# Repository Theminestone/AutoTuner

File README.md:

# AutoTuner
TFO Meran 2023 / 2024 - Maturaprojekt

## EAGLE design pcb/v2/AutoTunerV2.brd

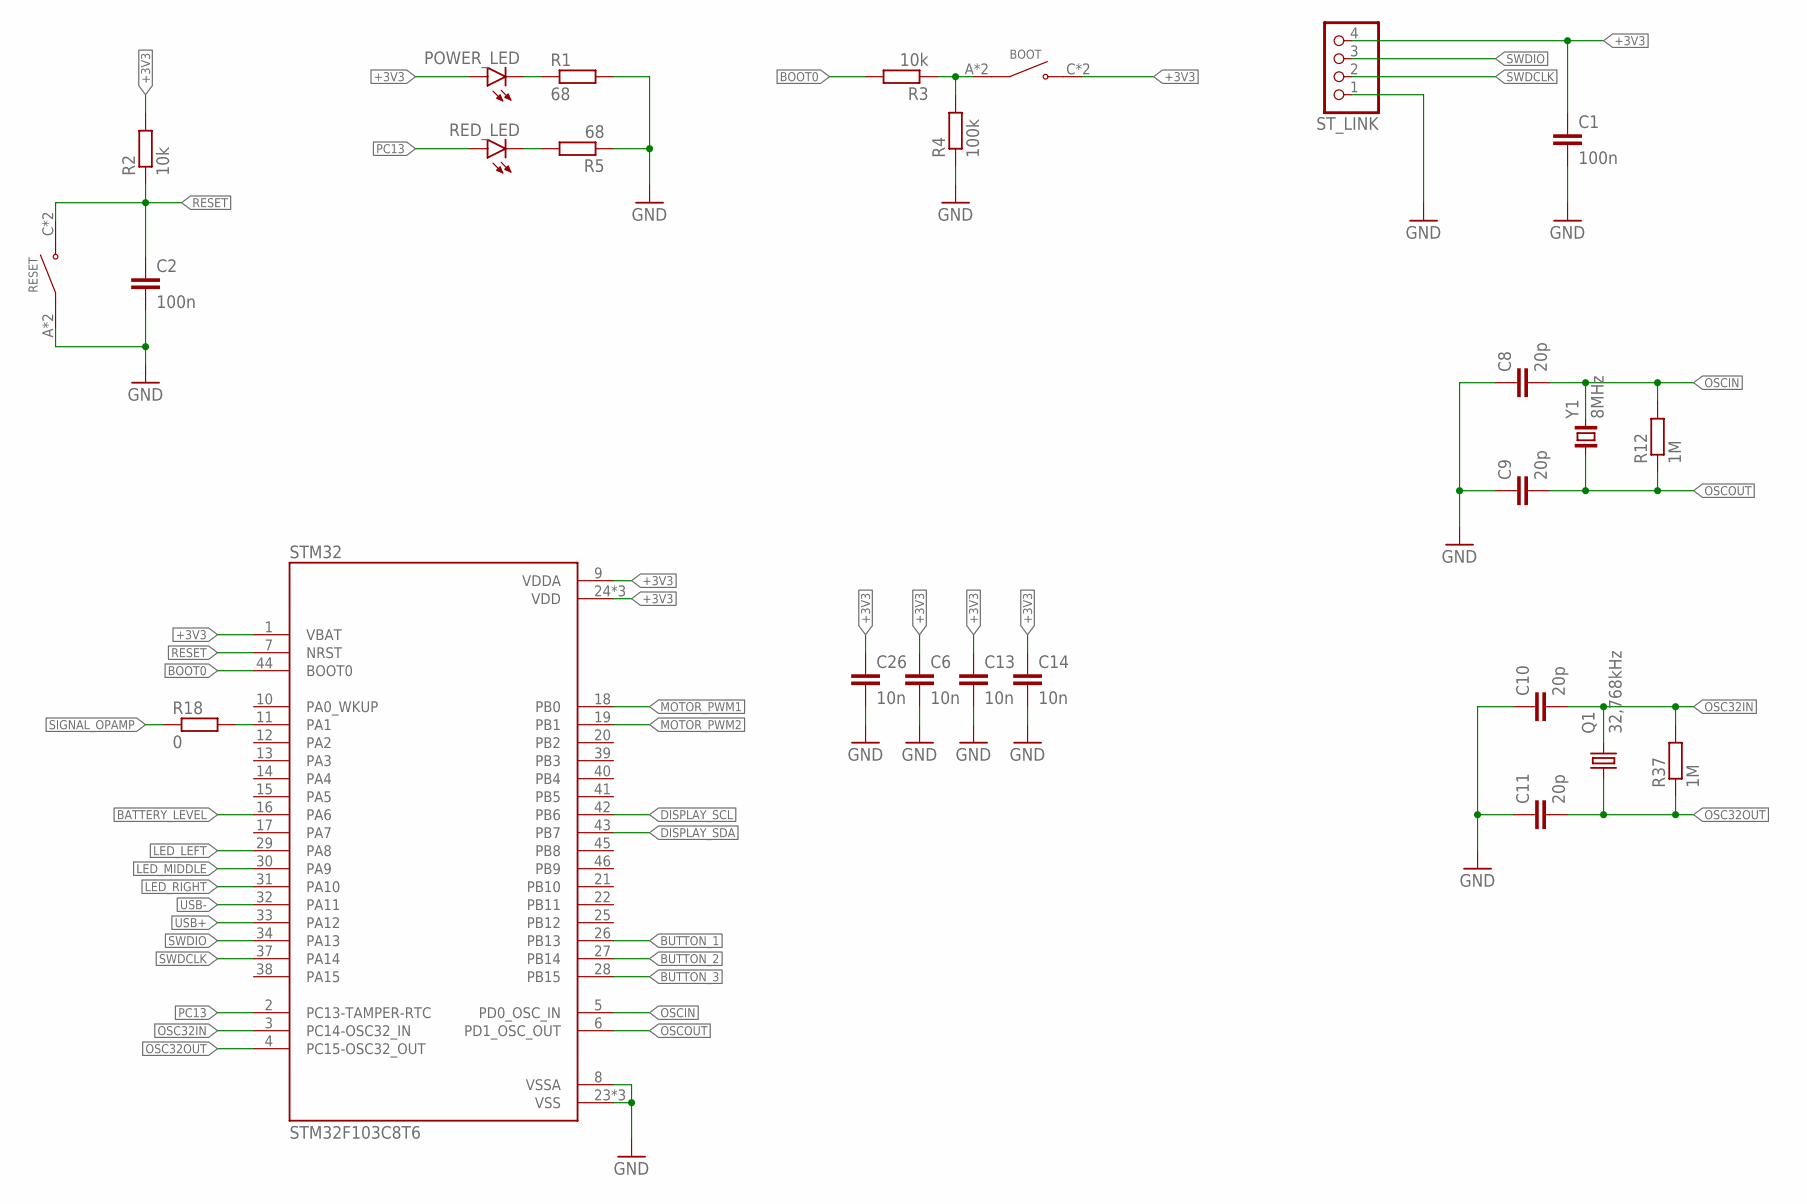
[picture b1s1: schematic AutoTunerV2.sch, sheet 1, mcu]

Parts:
BOOT: TS-1187A-B-A-B; SW_TS-1187A-B-A-B; LCSC_PART C318884
C1, C2: 100n; C0805
C6, C13, C14, C26: 10n; C0805
C8, C9, C10, C11: 20p; C0805
POWER_LED: LEDCHIPLED_0805; CHIPLED_0805; LCSC_PART C2297
Q1: 32,768kHz; 3.2X1.5; LCSC_PART C32346
R1, R5: 68; R0805; LCSC_PART C17802
R2, R3: 10k; R0805
R4: 100k; R0805
R12, R37: 1M; R0805
R18: 0; R0805
RED_LED: LEDCHIPLED_0805; CHIPLED_0805; LCSC_PART C84256
RESET: TS-1187A-B-A-B; SW_TS-1187A-B-A-B; LCSC_PART C318884
STM32: STM32F103C8T6; QFP50P900X900X160-48N; LCSC_PART C8734
ST_LINK: PINHD-1X4; 1X04
Y1: 8MHz; CRYSTAL_2-SMD-5X3; LCSC_PART C115962

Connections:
+3V3: BOOT.C (NO), BOOT.D (NO), C1.1, C6.1, C13.1, C14.1, C26.1, POWER_LED.A, R2.2, STM32.1 (VBAT), STM32.9 (VDDA), STM32.24 (VDD), STM32.36 (VDD), STM32.48 (VDD), ST_LINK.4; also elsewhere on the board
BATTERY_LEVEL: STM32.16 (PA6); also elsewhere on the board
BOOT0: R3.2, STM32.44 (BOOT0)
BUTTON_1: STM32.26 (PB13); also elsewhere on the board
BUTTON_2: STM32.27 (PB14); also elsewhere on the board
BUTTON_3: STM32.28 (PB15); also elsewhere on the board
DISPLAY_SCL: STM32.42 (PB6); also elsewhere on the board
DISPLAY_SDA: STM32.43 (PB7); also elsewhere on the board
GND: C1.2, C2.2, C6.2, C8.1, C9.1, C10.1, C11.1, C13.2, C14.2, C26.2, R1.2, R4.1, R5.1, RESET.A (COM), RESET.B (COM), STM32.8 (VSSA), STM32.23 (VSS), STM32.35 (VSS), STM32.47 (VSS), ST_LINK.1; also elsewhere on the board
LED_LEFT: STM32.29 (PA8); also elsewhere on the board
LED_MIDDLE: STM32.30 (PA9); also elsewhere on the board
LED_RIGHT: STM32.31 (PA10); also elsewhere on the board
MOTOR_PWM1: STM32.18 (PB0); also elsewhere on the board
MOTOR_PWM2: STM32.19 (PB1); also elsewhere on the board
unnamed: R5.2, RED_LED.C
unnamed: POWER_LED.C, R1.1
unnamed: BOOT.A (COM), BOOT.B (COM), R3.1, R4.2
unnamed: R18.2, STM32.11 (PA1)
OSC32IN: C10.2, Q1.2, R37.2, STM32.3 (PC14-OSC32_IN)
OSC32OUT: C11.2, Q1.1, R37.1, STM32.4 (PC15-OSC32_OUT)
OSCIN: C8.2, R12.2, STM32.5 (PD0_OSC_IN), Y1.2
OSCOUT: C9.2, R12.1, STM32.6 (PD1_OSC_OUT), Y1.1
PC13: RED_LED.A, STM32.2 (PC13-TAMPER-RTC)
RESET: C2.1, R2.1, RESET.C (NO), RESET.D (NO), STM32.7 (NRST)
SIGNAL_OPAMP: R18.1; also elsewhere on the board
SWDCLK: STM32.37 (PA14), ST_LINK.2
SWDIO: STM32.34 (PA13), ST_LINK.3
USB+: STM32.33 (PA12); also elsewhere on the board
USB-: STM32.32 (PA11); also elsewhere on the board

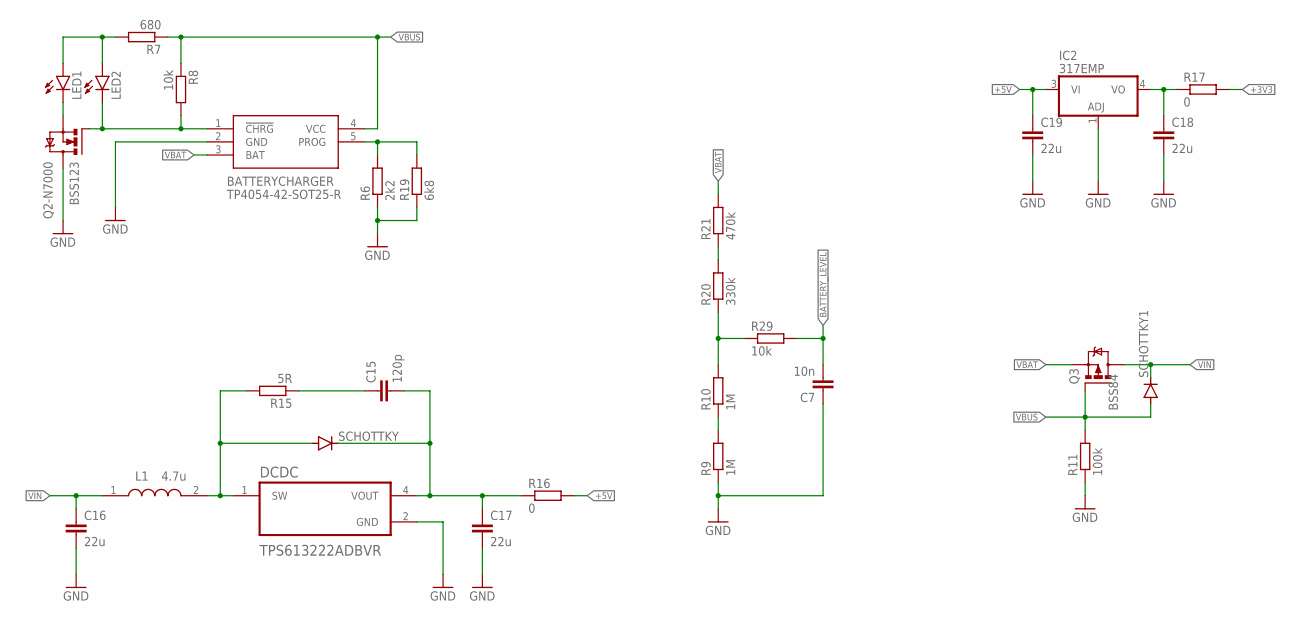
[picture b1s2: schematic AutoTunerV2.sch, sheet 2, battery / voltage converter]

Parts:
BATTERYCHARGER: TP4054-42-SOT25-R; SOT95P280X100-5N; LCSC_PART C32574
C7: 10n; C0805
C15: 120p; C0805
C16, C17, C18, C19: 22u; C1206; LCSC_PART C5672
DCDC: TPS613222ADBVR; SOT95P280X145-5N; LCSC_PART C2071163
IC2: 317EMP; SOT223; LCSC_PART C6186
L1: 4.7u; DFE2HCAH1R0MJ0L; LCSC_PART C3093670
LED1: LEDCHIPLED_0805; CHIPLED_0805; LCSC_PART C2297
LED2: LEDCHIPLED_0805; CHIPLED_0805; LCSC_PART C84256
Q2-N7000: BSS123; SOT23; LCSC_PART C20917
Q3: BSS84; SOT23; LCSC_PARTS C10487
R6: 2k2; R0805
R7: 680; R0805
R8, R29: 10k; R0805
R9, R10: 1M; R0805
R11: 100k; R0805
R15: 5R; R0805
R16, R17: 0; R0805
R19: 6k8; R0805
R20: 330k; R0805
R21: 470k; R0805
SCHOTTKY, SCHOTTKY1: DIODE-SOD323-R; SOD323-R; LCSC_PART C191023

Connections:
+3V3: R17.2; also elsewhere on the board
+5V: C19.1, IC2.3 (VI), R16.2; also elsewhere on the board
BATTERY_LEVEL: C7.2, R29.2; also elsewhere on the board
GND: BATTERYCHARGER.2 (GND), C7.1, C16.2, C17.2, C18.2, C19.2, DCDC.2 (GND), IC2.1 (ADJ), Q2-N7000.3 (D), R6.1, R9.1, R11.1, R19.1; also elsewhere on the board
unnamed: DCDC.1 (SW), L1.2, R15.2, SCHOTTKY.A
unnamed: R9.2, R10.1
unnamed: C15.2, C17.1, DCDC.4 (VOUT), R16.1, SCHOTTKY.C
unnamed: BATTERYCHARGER.5 (PROG), R6.2, R19.2
unnamed: BATTERYCHARGER.1 (!CHRG), LED2.C, Q2-N7000.1 (G), R8.2
unnamed: C15.1, R15.1
unnamed: LED1.A, LED2.A, R7.2
unnamed: LED1.C, Q2-N7000.2 (S)
unnamed: C18.1, IC2.4 (VO), R17.1
unnamed: R20.2, R21.1
unnamed: R10.2, R20.1, R29.1
VBAT: BATTERYCHARGER.3 (BAT), Q3.2 (S), R21.2; also elsewhere on the board
VBUS: BATTERYCHARGER.4 (VCC), Q3.1 (G), R7.1, R8.1, R11.2, SCHOTTKY1.A; also elsewhere on the board
VIN: C16.1, L1.1, Q3.3 (D), SCHOTTKY1.C

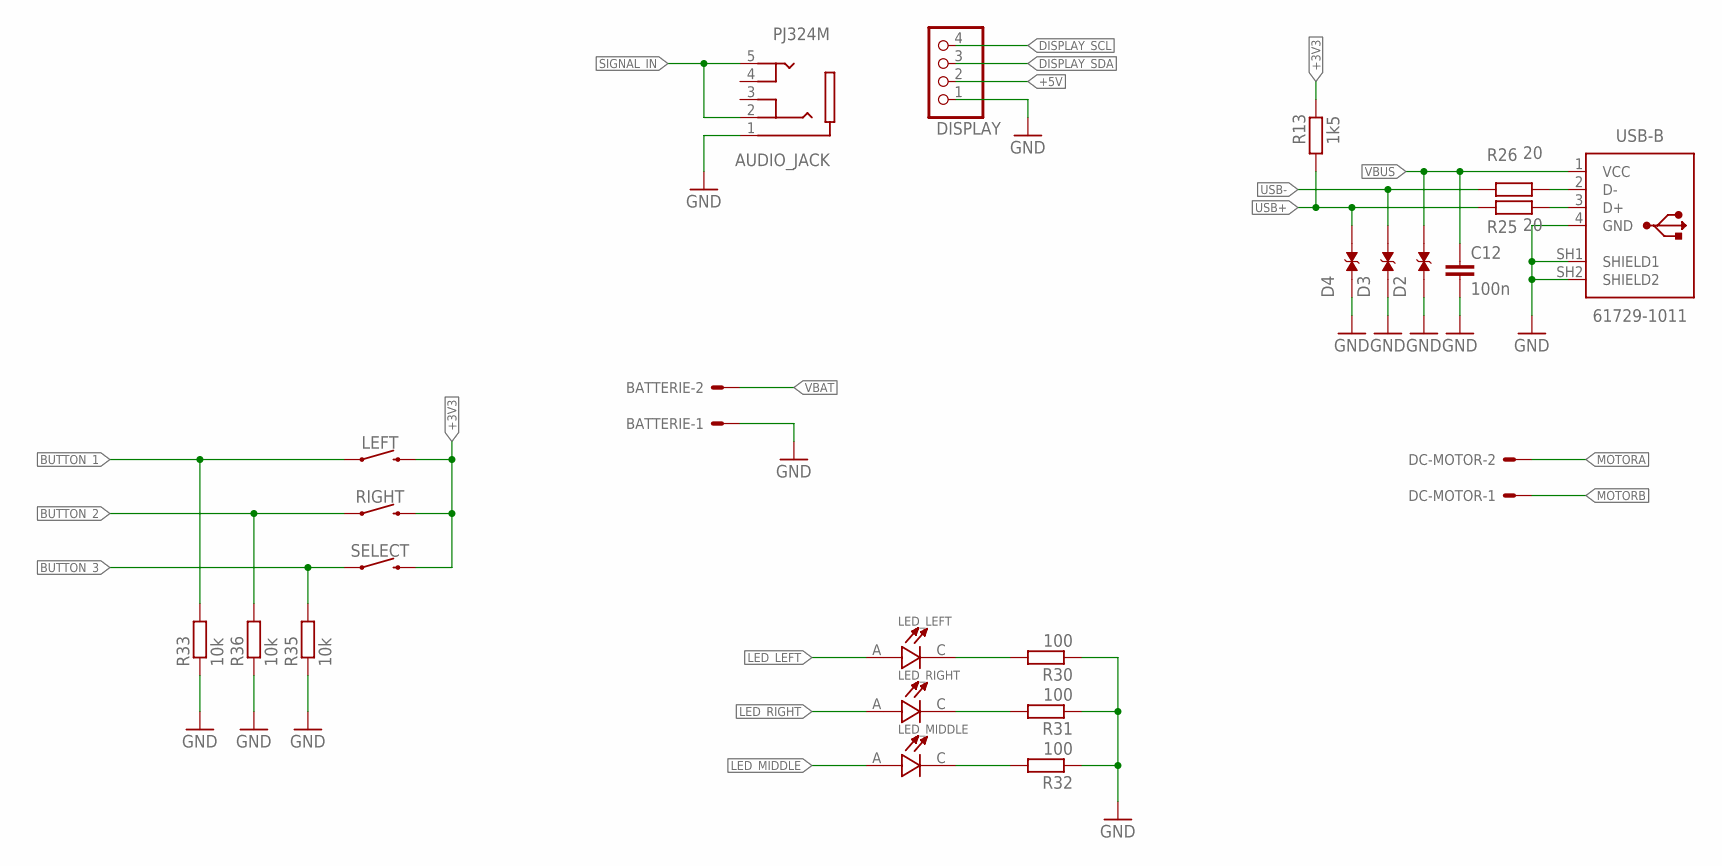
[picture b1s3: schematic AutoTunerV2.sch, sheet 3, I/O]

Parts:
AUDIO_JACK: PJ324M; WENZHOU_PJ324M
BATTERIE: 22-27-2021-02; 6410-02
C12: 100n; C0805
D2, D3, D4: TESD5V0L1UC_RJG; DIO_TESD5V0L1UC_RJG; LCSC_PART C7420372
DC-MOTOR: 22-27-2021-02; 6410-02
DISPLAY: PINHD-1X4; 1X04
LED_LEFT: L-53GD; LEDRD254W50D500H1060
LED_MIDDLE: L-53GD; LEDRD254W50D500H1060
LED_RIGHT: L-53GD; LEDRD254W50D500H1060
LEFT: MOMENTARY-SWITCH-SPST-PTH-12MM; TACTILE_SWITCH_PTH_12MM
R13: 1k5; R0805
R25, R26: 20; R0805
R30, R31, R32: 100; R0805
R33, R35, R36: 10k; R0805
RIGHT: MOMENTARY-SWITCH-SPST-PTH-12MM; TACTILE_SWITCH_PTH_12MM
SELECT: MOMENTARY-SWITCH-SPST-PTH-12MM; TACTILE_SWITCH_PTH_12MM
USB-B: 61729-1011; 61729-1011BLF

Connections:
+3V3: LEFT.3 (2), R13.2, RIGHT.3 (2), SELECT.3 (2); also elsewhere on the board
+5V: DISPLAY.2; also elsewhere on the board
BUTTON_1: LEFT.1, R33.2; also elsewhere on the board
BUTTON_2: R36.2, RIGHT.1; also elsewhere on the board
BUTTON_3: R35.2, SELECT.1; also elsewhere on the board
DISPLAY_SCL: DISPLAY.4; also elsewhere on the board
DISPLAY_SDA: DISPLAY.3; also elsewhere on the board
GND: AUDIO_JACK.1 (SLEEVE), BATTERIE.1, C12.2, D2.1, D3.1, D4.1, DISPLAY.1, R30.1, R31.1, R32.1, R33.1, R35.1, R36.1, USB-B.4 (GND), USB-B.SH1 (SHIELD1), USB-B.SH2 (SHIELD2); also elsewhere on the board
LED_LEFT: LED_LEFT.A; also elsewhere on the board
LED_MIDDLE: LED_MIDDLE.A; also elsewhere on the board
LED_RIGHT: LED_RIGHT.A; also elsewhere on the board
MOTORA: DC-MOTOR.2; also elsewhere on the board
MOTORB: DC-MOTOR.1; also elsewhere on the board
unnamed: LED_LEFT.C, R30.2
unnamed: LED_RIGHT.C, R31.2
unnamed: LED_MIDDLE.C, R32.2
unnamed: R25.2, USB-B.3 (D+)
unnamed: R26.2, USB-B.2 (D-)
SIGNAL_IN: AUDIO_JACK.2 (RING_1), AUDIO_JACK.5 (TIP_2); also elsewhere on the board
USB+: D4.2, R13.1, R25.1; also elsewhere on the board
USB-: D3.2, R26.1; also elsewhere on the board
VBAT: BATTERIE.2; also elsewhere on the board
VBUS: C12.1, D2.2, USB-B.1 (VCC); also elsewhere on the board

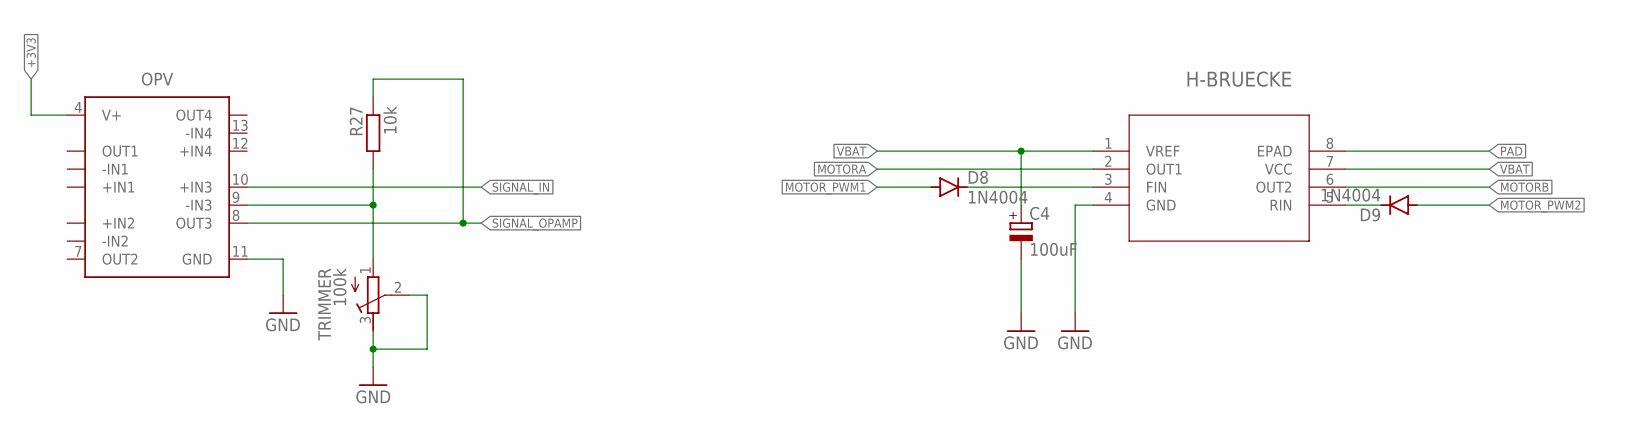
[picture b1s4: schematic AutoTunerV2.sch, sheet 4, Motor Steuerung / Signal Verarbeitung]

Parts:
C4: 100uF; B45181A
D8, D9: 1N4004; DO41-10
H-BRUECKE: BD6222HFP-TRHRP7_ROM-M; HRP7_ROM-M
OPV: LM324_SOIC; SOIC127P600X175-14N; LCSC_PART C71035
R27: 10k; R0805
TRIMMER: 100k; RTRIM64Y

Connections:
+3V3: OPV.4 (V+); also elsewhere on the board
GND: C4.-, H-BRUECKE.4 (GND), OPV.11 (GND), TRIMMER.2 (S), TRIMMER.3 (E); also elsewhere on the board
MOTORA: H-BRUECKE.2 (OUT1); also elsewhere on the board
MOTORB: H-BRUECKE.6 (OUT2); also elsewhere on the board
MOTOR_PWM1: D8.A; also elsewhere on the board
MOTOR_PWM2: D9.A; also elsewhere on the board
unnamed: D8.C, H-BRUECKE.3 (FIN)
unnamed: D9.C, H-BRUECKE.5 (RIN)
unnamed: OPV.9 (-IN3), R27.2, TRIMMER.1 (A)
PAD: H-BRUECKE.8 (EPAD)
SIGNAL_IN: OPV.10 (+IN3); also elsewhere on the board
SIGNAL_OPAMP: OPV.8 (OUT3), R27.1; also elsewhere on the board
VBAT: C4.+, H-BRUECKE.1 (VREF), H-BRUECKE.7 (VCC); also elsewhere on the board

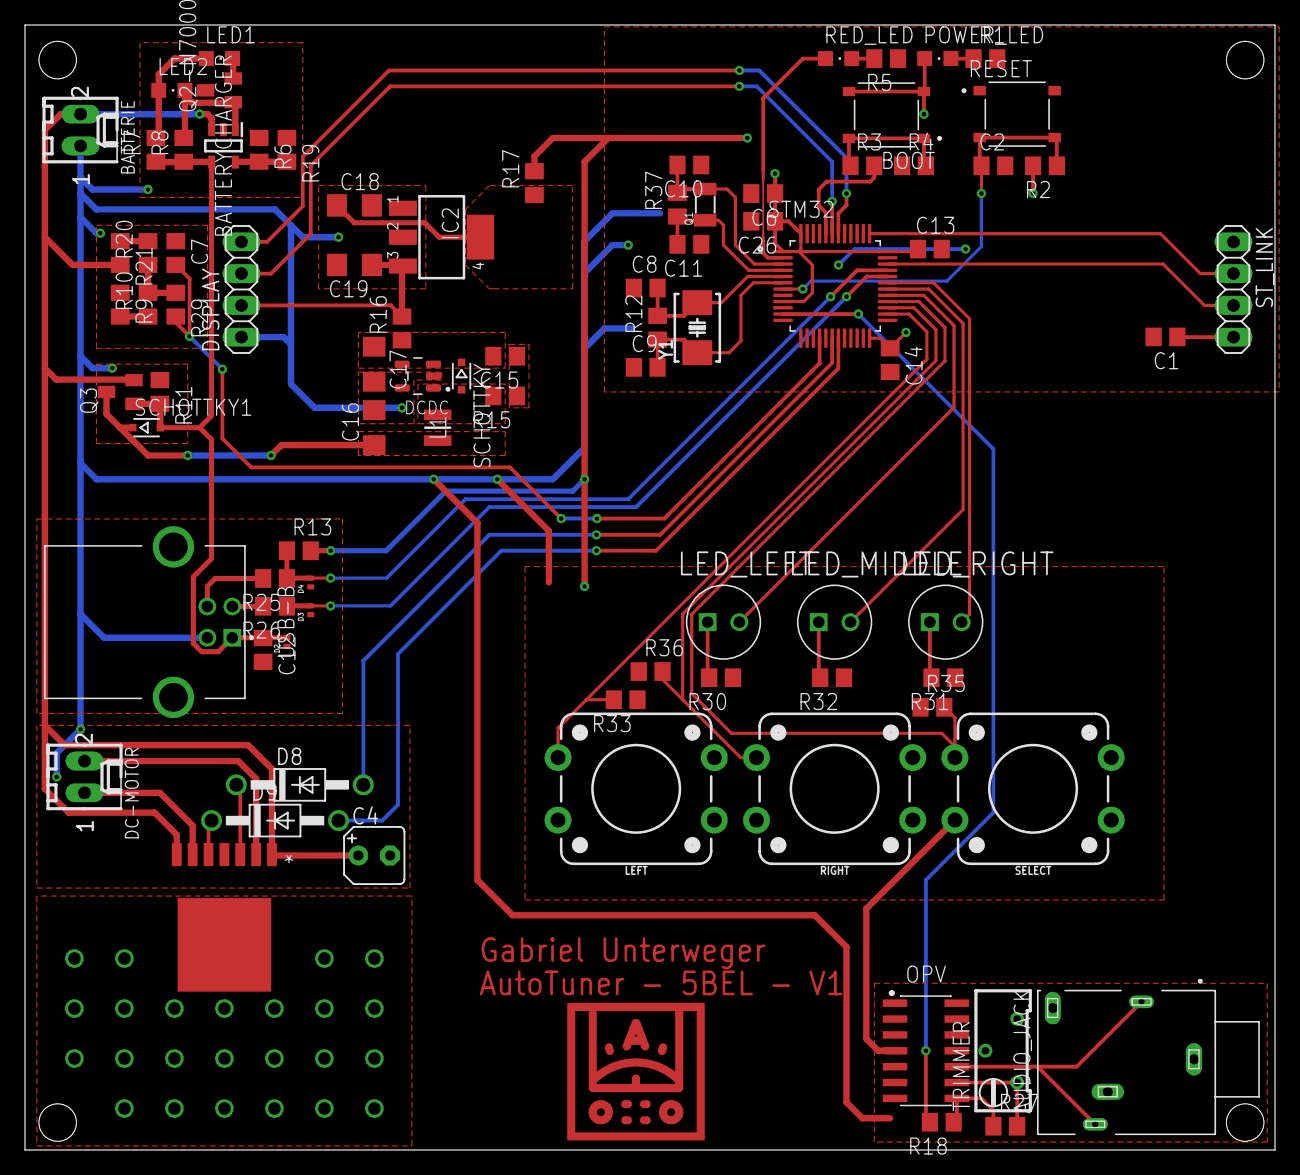
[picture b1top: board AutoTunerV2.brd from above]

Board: 2 copper layers, 100.0 x 90.0 mm, 86 parts (0 on the bottom side), 55 nets.

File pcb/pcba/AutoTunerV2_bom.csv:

Comment,Designator,Footprint,LCSC Part #
,DISPLAY,1X04,
,ST_LINK,1X04,
,BATTERIE,6410-02,
,DC-MOTOR,6410-02,
,LED1,CHIPLED_0805,C2297
,LED2,CHIPLED_0805,C84256
,POWER_LED,CHIPLED_0805,C2297
,RED_LED,CHIPLED_0805,C84256
,D2,DIO_TESD5V0L1UC_RJG,C7420372
,D3,DIO_TESD5V0L1UC_RJG,C7420372
,D4,DIO_TESD5V0L1UC_RJG,C7420372
,H-BRUECKE,HRP7_ROM-M,
,LED_LEFT,LEDRD254W50D500H1060,
,LED_MIDDLE,LEDRD254W50D500H1060,
,LED_RIGHT,LEDRD254W50D500H1060,
,SCHOTTKY,SOD323-R,C191023
,SCHOTTKY1,SOD323-R,C191023
,OPV,SOIC127P600X175-14N,C71035
,BOOT,SW_TS-1187A-B-A-B,C318884
,RESET,SW_TS-1187A-B-A-B,C318884
0,R16 R17 R18,R0805,
1M,R9 R10 R12 R37,R0805,
1N4004,D8 D9,DO41-10,
1k5,R13,R0805,
2k2,R6,R0805,
4.7u,L1,DFE2HCAH1R0MJ0L,C391306
5R,R15,R0805,
6k8,R19,R0805,
8MHz,Y1,CRYSTAL_2-SMD-5X3,C115962
10k,R2 R3 R8 R27 R29 R33 R35 R36,R0805,
10n,C6 C7 C13 C14 C26,C0805,
20,R25 R26,R0805,
20p,C8 C9 C10 C11,C0805,
22u,C16 C17 C18 C19,C1206,C5672
32 768kHz,Q1,3.2X1.5,C32346
68,R1 R5,R0805,C17802
100,R30 R31 R32,R0805,
100k,R4 R11,R0805,
100k,TRIMMER,RTRIM64Y,
100n,C1 C2 C12,C0805,
100uF,C4,B45181A,
120p,C15,C0805,
317EMP,IC2,SOT223,C6186
330k,R20,R0805,
470k,R21,R0805,
680,R7,R0805,
61729-1011,USB-B,61729-1011BLF,
BSS84,Q3,SOT23,
BSS123,Q2,SOT23,C20917
MOMENTARY-SWITCH-SPST-PTH-12MM,LEFT RIGHT SELECT,TACTILE_SWITCH_PTH_12MM,
PJ324M,AUDIO_JACK,WENZHOU_PJ324M,
STM32F103C8T6,STM32,QFP50P900X900X160-48N,C8734
TP4054-42-SOT25-R,BATTERYCHARGER,SOT95P280X100-5N,C32574
TPS613222ADBVR,DCDC,SOT95P280X145-5N,C2071163

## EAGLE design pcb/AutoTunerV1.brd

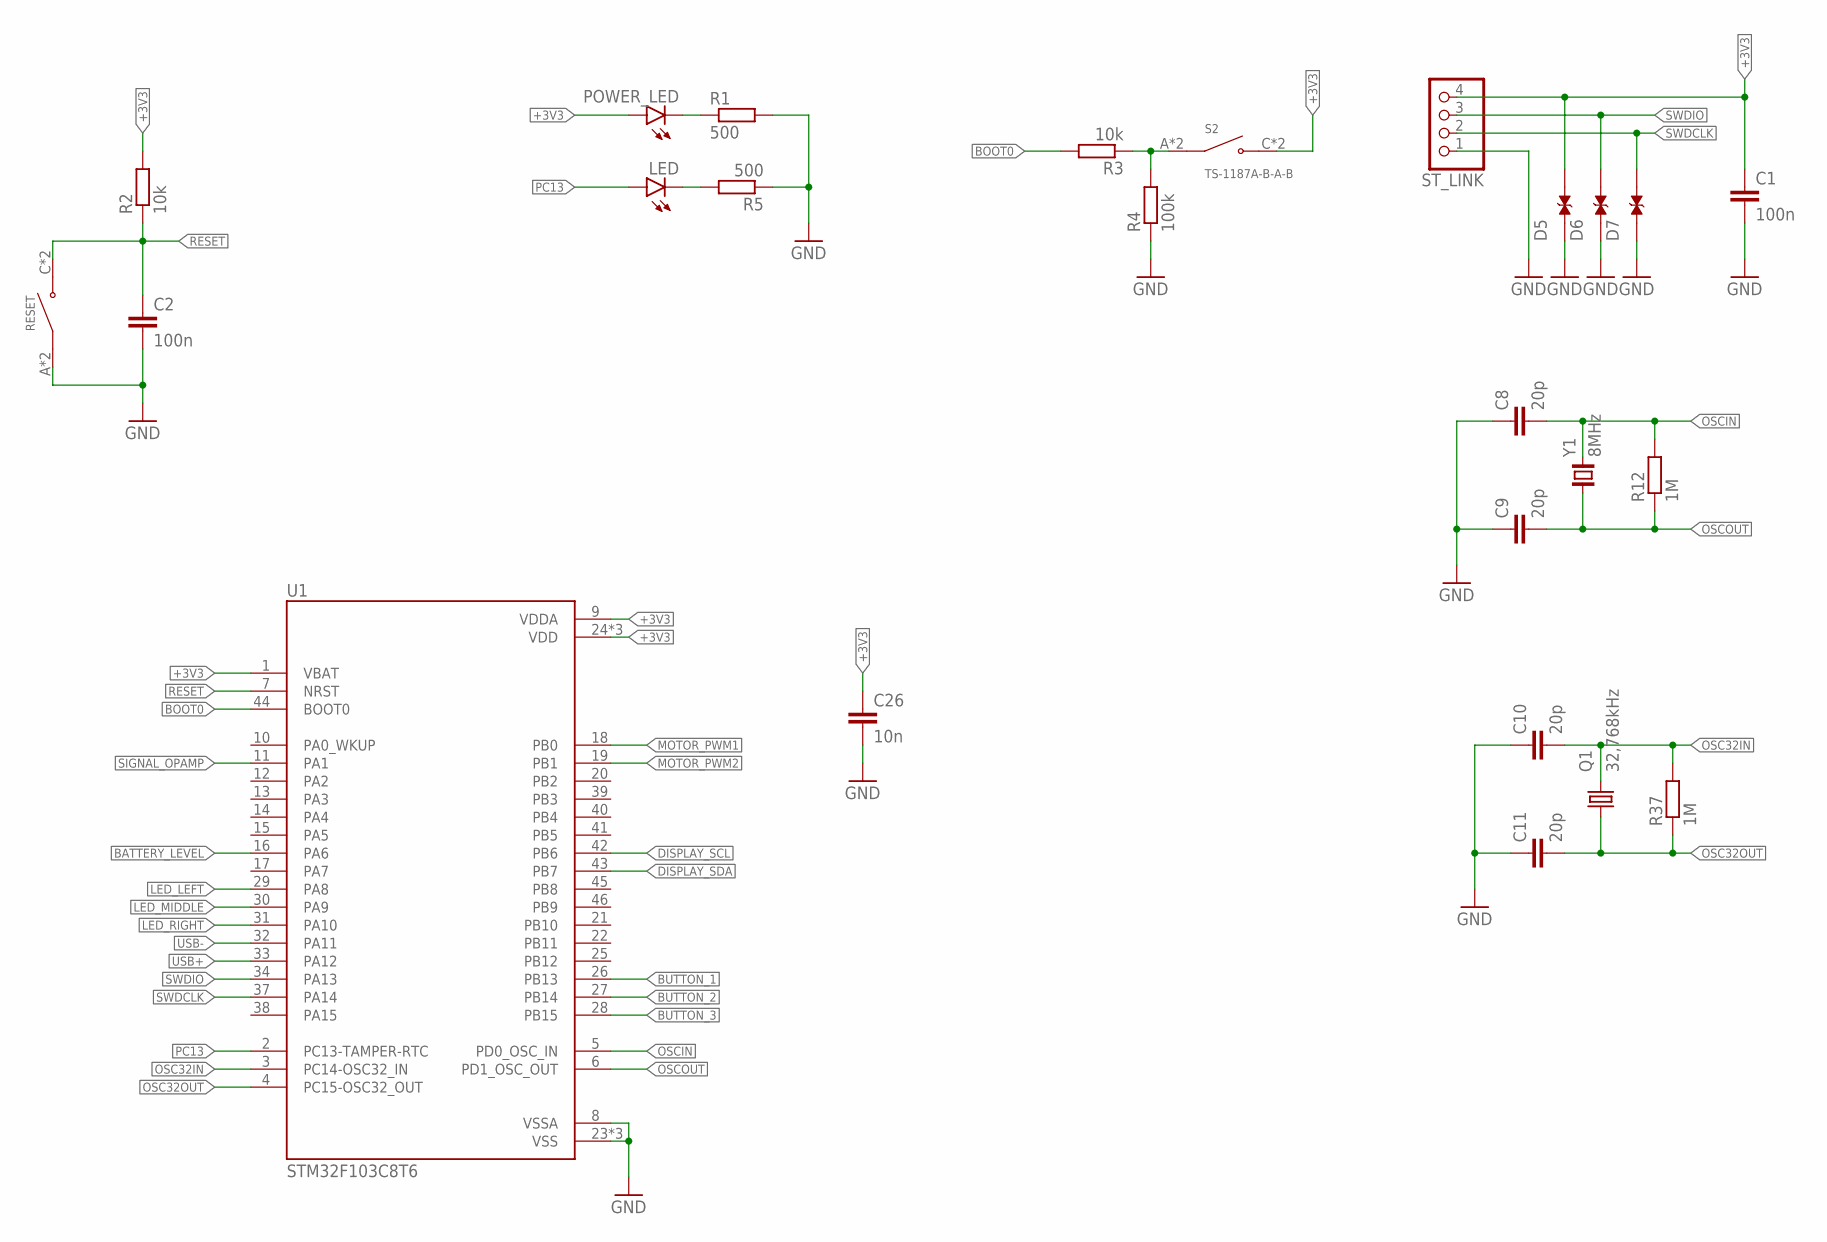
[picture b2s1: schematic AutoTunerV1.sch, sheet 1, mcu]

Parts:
C1, C2: 100n; C0805
C8, C9, C10, C11: 20p; C0805
C26: 10n; C0805
D5, D6, D7: TESD5V0L1UC_RJG; DIO_TESD5V0L1UC_RJG; LCSC_PART C7420372
LED: LEDCHIPLED_0805; CHIPLED_0805
POWER_LED: LEDCHIPLED_0805; CHIPLED_0805
Q1: 32,768kHz; 3.2X1.5; LCSC_PART C32346
R1, R5: 500; R0805
R2, R3: 10k; R0805
R4: 100k; R0805
R12, R37: 1M; R0805
RESET: TS-1187A-B-A-B; SW_TS-1187A-B-A-B; LCSC_PART C318884
S2: TS-1187A-B-A-B; SW_TS-1187A-B-A-B; LCSC_PART C318884
ST_LINK: PINHD-1X4; 1X04
U1: STM32F103C8T6; QFP50P900X900X160-48N; LCSC_PART C8734
Y1: 8MHz; CRYSTAL_2-SMD-5X3; LCSC_PART C115962

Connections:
+3V3: C1.1, C26.1, D5.2, POWER_LED.A, R2.2, S2.C (NO), S2.D (NO), ST_LINK.4, U1.1 (VBAT), U1.9 (VDDA), U1.24 (VDD), U1.36 (VDD), U1.48 (VDD); also elsewhere on the board
BATTERY_LEVEL: U1.16 (PA6); also elsewhere on the board
BOOT0: R3.2, U1.44 (BOOT0)
BUTTON_1: U1.26 (PB13); also elsewhere on the board
BUTTON_2: U1.27 (PB14); also elsewhere on the board
BUTTON_3: U1.28 (PB15); also elsewhere on the board
DISPLAY_SCL: U1.42 (PB6); also elsewhere on the board
DISPLAY_SDA: U1.43 (PB7); also elsewhere on the board
GND: C1.2, C2.2, C8.1, C9.1, C10.1, C11.1, C26.2, D5.1, D6.1, D7.1, R1.2, R4.1, R5.1, RESET.A (COM), RESET.B (COM), ST_LINK.1, U1.8 (VSSA), U1.23 (VSS), U1.35 (VSS), U1.47 (VSS); also elsewhere on the board
LED_LEFT: U1.29 (PA8); also elsewhere on the board
LED_MIDDLE: U1.30 (PA9); also elsewhere on the board
LED_RIGHT: U1.31 (PA10); also elsewhere on the board
MOTOR_PWM1: U1.18 (PB0); also elsewhere on the board
MOTOR_PWM2: U1.19 (PB1); also elsewhere on the board
unnamed: LED.C, R5.2
unnamed: POWER_LED.C, R1.1
unnamed: R3.1, R4.2, S2.A (COM), S2.B (COM)
OSC32IN: C10.2, Q1.2, R37.2, U1.3 (PC14-OSC32_IN)
OSC32OUT: C11.2, Q1.1, R37.1, U1.4 (PC15-OSC32_OUT)
OSCIN: C8.2, R12.2, U1.5 (PD0_OSC_IN), Y1.2
OSCOUT: C9.2, R12.1, U1.6 (PD1_OSC_OUT), Y1.1
PC13: LED.A, U1.2 (PC13-TAMPER-RTC)
RESET: C2.1, R2.1, RESET.C (NO), RESET.D (NO), U1.7 (NRST)
SIGNAL_OPAMP: U1.11 (PA1); also elsewhere on the board
SWDCLK: D7.2, ST_LINK.2, U1.37 (PA14)
SWDIO: D6.2, ST_LINK.3, U1.34 (PA13)
USB+: U1.33 (PA12); also elsewhere on the board
USB-: U1.32 (PA11); also elsewhere on the board

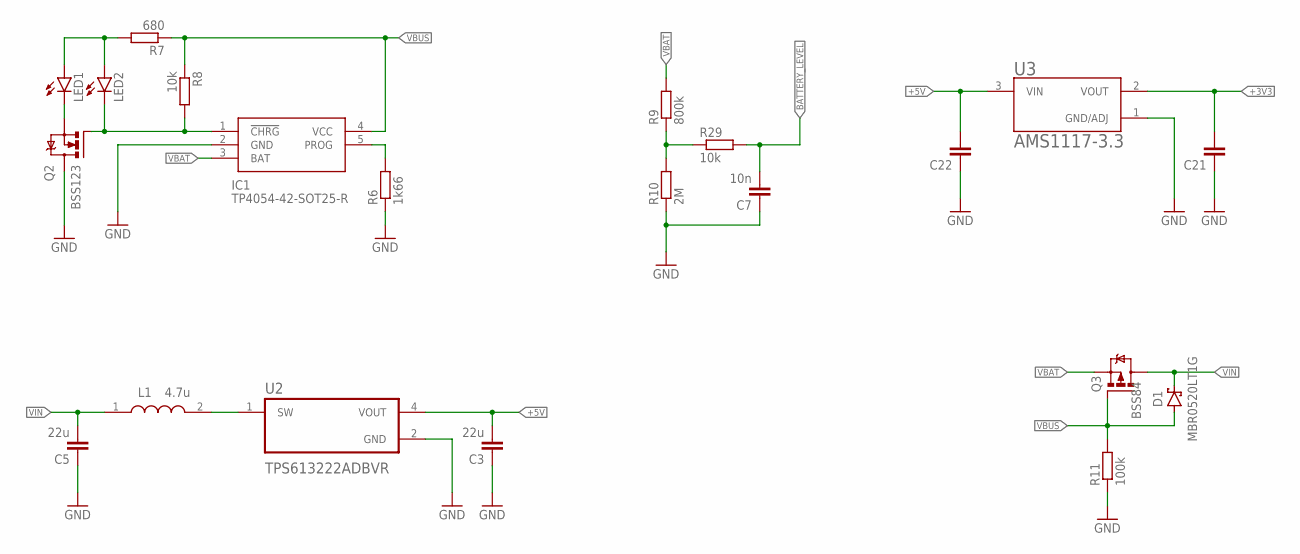
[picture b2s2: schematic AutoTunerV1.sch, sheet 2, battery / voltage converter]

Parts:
C3, C5: 22u; C0805
C7: 10n; C0805
C21, C22: C-EUC0805; C0805
D1: MBR0520LT1G; SODFL3718X115; LCSC_PART C191023
IC1: TP4054-42-SOT25-R; SOT95P280X100-5N; LCSC_PART C32574
L1: 4.7u; DFE2HCAH1R0MJ0L; LCSC_PART C391306
LED1, LED2: LEDCHIPLED_0805; CHIPLED_0805
Q2: BSS123; SOT23; LCSC_PART C20917
Q3: BSS84; SOT23; LCSC_PARTS C10487
R6: 1k66; R0805
R7: 680; R0805
R8, R29: 10k; R0805
R9: 800k; R0805
R10: 2M; R0805
R11: 100k; R0805
U2: TPS613222ADBVR; SOT95P280X145-5N; LCSC_PART C2071163
U3: AMS1117-3.3; SOT229P700X180-4N; LCSC_PART C6186

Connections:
+3V3: C21.2, U3.2 (VOUT); also elsewhere on the board
+5V: C3.2, C22.2, U2.4 (VOUT), U3.3 (VIN); also elsewhere on the board
BATTERY_LEVEL: C7.2, R29.2; also elsewhere on the board
GND: C3.1, C5.1, C7.1, C21.1, C22.1, IC1.2 (GND), Q2.3 (D), R6.1, R10.1, R11.1, U2.2 (GND), U3.1 (GND/ADJ); also elsewhere on the board
unnamed: L1.2, U2.1 (SW)
unnamed: R9.1, R10.2, R29.1
unnamed: IC1.5 (PROG), R6.2
unnamed: IC1.1 (!CHRG), LED2.C, Q2.1 (G), R8.2
unnamed: LED1.A, LED2.A, R7.2
unnamed: LED1.C, Q2.2 (S)
VBAT: IC1.3 (BAT), Q3.2 (S), R9.2; also elsewhere on the board
VBUS: D1.2 (A), IC1.4 (VCC), Q3.1 (G), R7.1, R8.1, R11.2; also elsewhere on the board
VIN: C5.2, D1.1 (C), L1.1, Q3.3 (D)

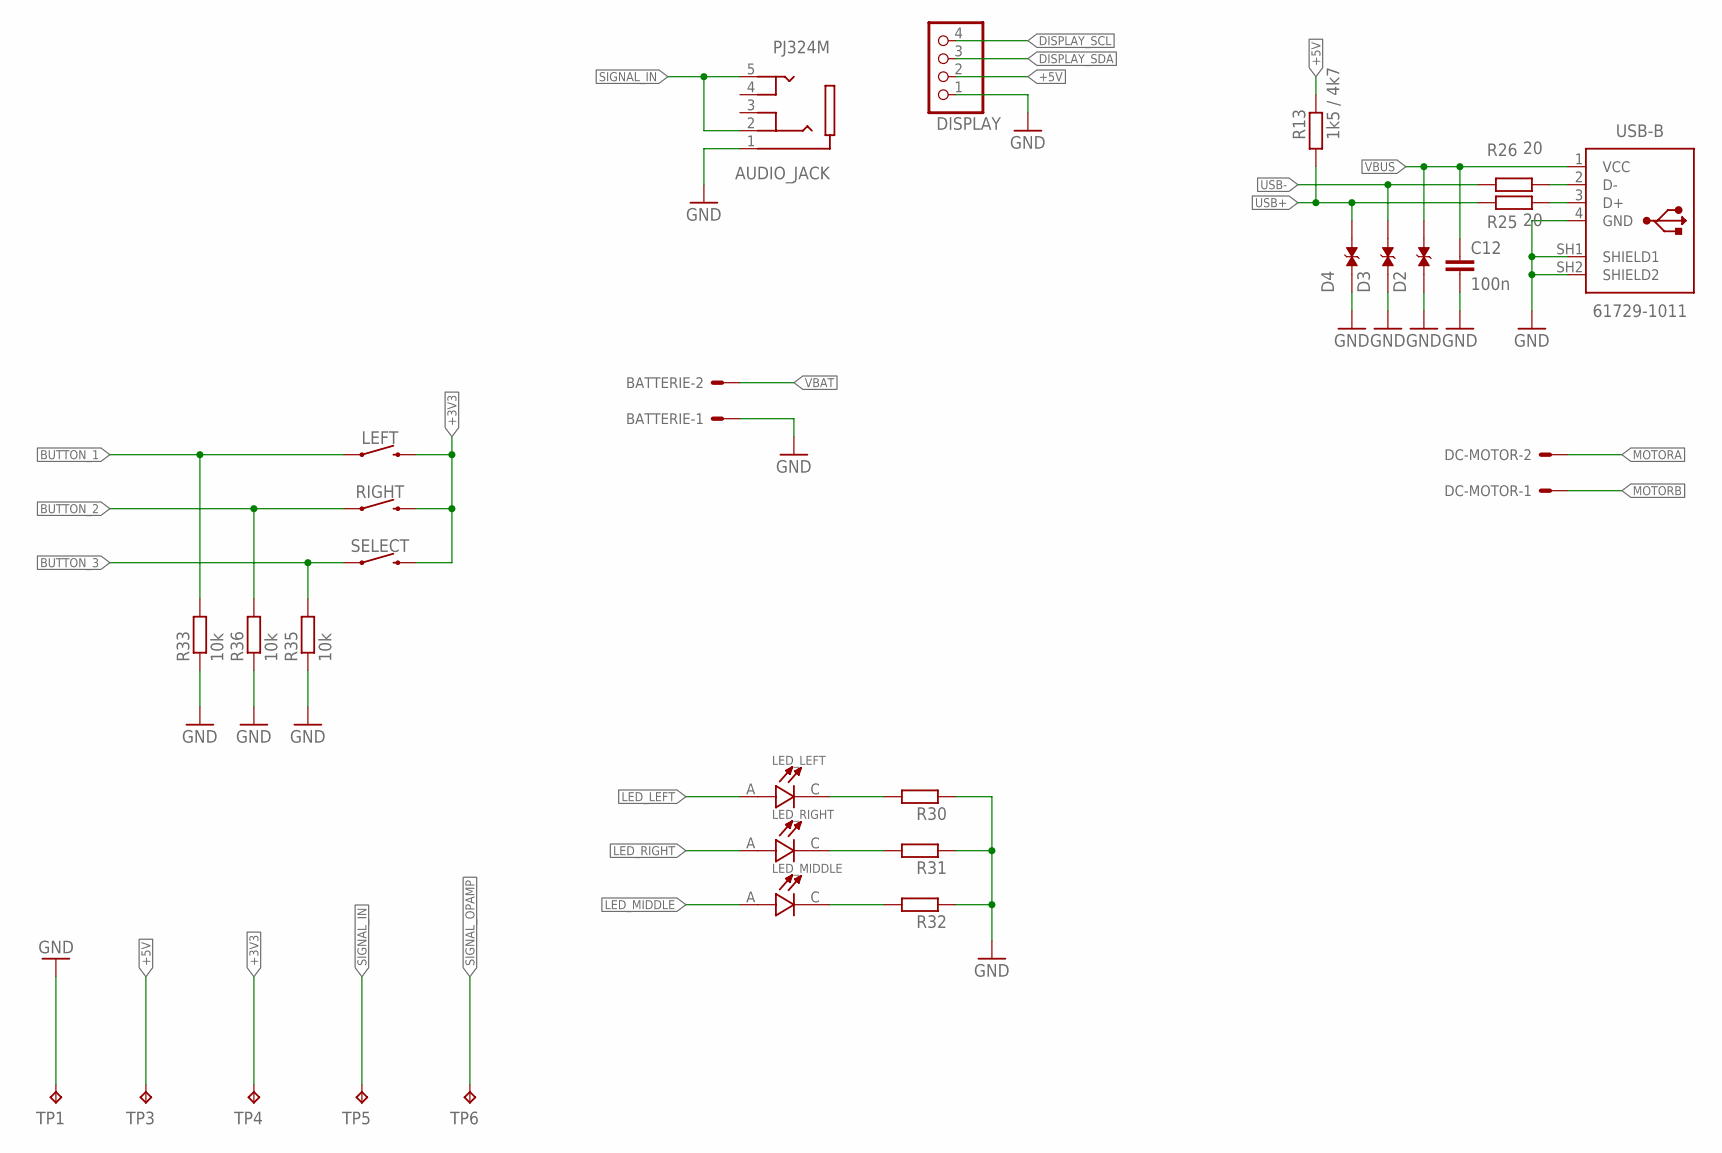
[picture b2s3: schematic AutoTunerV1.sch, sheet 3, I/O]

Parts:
AUDIO_JACK: PJ324M; WENZHOU_PJ324M
BATTERIE: 22-27-2021-02; 6410-02
C12: 100n; C0805
D2, D3, D4: TESD5V0L1UC_RJG; DIO_TESD5V0L1UC_RJG; LCSC_PART C7420372
DC-MOTOR: 22-27-2021-02; 6410-02
DISPLAY: PINHD-1X4; 1X04
LED_LEFT: L-53GD; LEDRD254W50D500H1060
LED_MIDDLE: L-53GD; LEDRD254W50D500H1060
LED_RIGHT: L-53GD; LEDRD254W50D500H1060
LEFT: MOMENTARY-SWITCH-SPST-PTH-12MM; TACTILE_SWITCH_PTH_12MM
R13: 1k5 / 4k7; R0805
R25, R26: 20; R0805
R30, R31, R32: R-EU_R0805; R0805
R33, R35, R36: 10k; R0805
RIGHT: MOMENTARY-SWITCH-SPST-PTH-12MM; TACTILE_SWITCH_PTH_12MM
SELECT: MOMENTARY-SWITCH-SPST-PTH-12MM; TACTILE_SWITCH_PTH_12MM
TP1, TP3, TP4, TP5, TP6: TPB1,27; B1,27
USB-B: 61729-1011; 61729-1011BLF

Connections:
+3V3: LEFT.3 (2), RIGHT.3 (2), SELECT.3 (2), TP4.TP; also elsewhere on the board
+5V: DISPLAY.2, R13.2, TP3.TP; also elsewhere on the board
BUTTON_1: LEFT.1, R33.2; also elsewhere on the board
BUTTON_2: R36.2, RIGHT.1; also elsewhere on the board
BUTTON_3: R35.2, SELECT.1; also elsewhere on the board
DISPLAY_SCL: DISPLAY.4; also elsewhere on the board
DISPLAY_SDA: DISPLAY.3; also elsewhere on the board
GND: AUDIO_JACK.1 (SLEEVE), BATTERIE.1, C12.2, D2.1, D3.1, D4.1, DISPLAY.1, R30.1, R31.1, R32.1, R33.1, R35.1, R36.1, TP1.TP, USB-B.4 (GND), USB-B.SH1 (SHIELD1), USB-B.SH2 (SHIELD2); also elsewhere on the board
LED_LEFT: LED_LEFT.A; also elsewhere on the board
LED_MIDDLE: LED_MIDDLE.A; also elsewhere on the board
LED_RIGHT: LED_RIGHT.A; also elsewhere on the board
MOTORA: DC-MOTOR.2; also elsewhere on the board
MOTORB: DC-MOTOR.1; also elsewhere on the board
unnamed: LED_LEFT.C, R30.2
unnamed: LED_RIGHT.C, R31.2
unnamed: LED_MIDDLE.C, R32.2
unnamed: R25.2, USB-B.3 (D+)
unnamed: R26.2, USB-B.2 (D-)
SIGNAL_IN: AUDIO_JACK.2 (RING_1), AUDIO_JACK.5 (TIP_2), TP5.TP; also elsewhere on the board
SIGNAL_OPAMP: TP6.TP; also elsewhere on the board
USB+: D4.2, R13.1, R25.1; also elsewhere on the board
USB-: D3.2, R26.1; also elsewhere on the board
VBAT: BATTERIE.2; also elsewhere on the board
VBUS: C12.1, D2.2, USB-B.1 (VCC); also elsewhere on the board

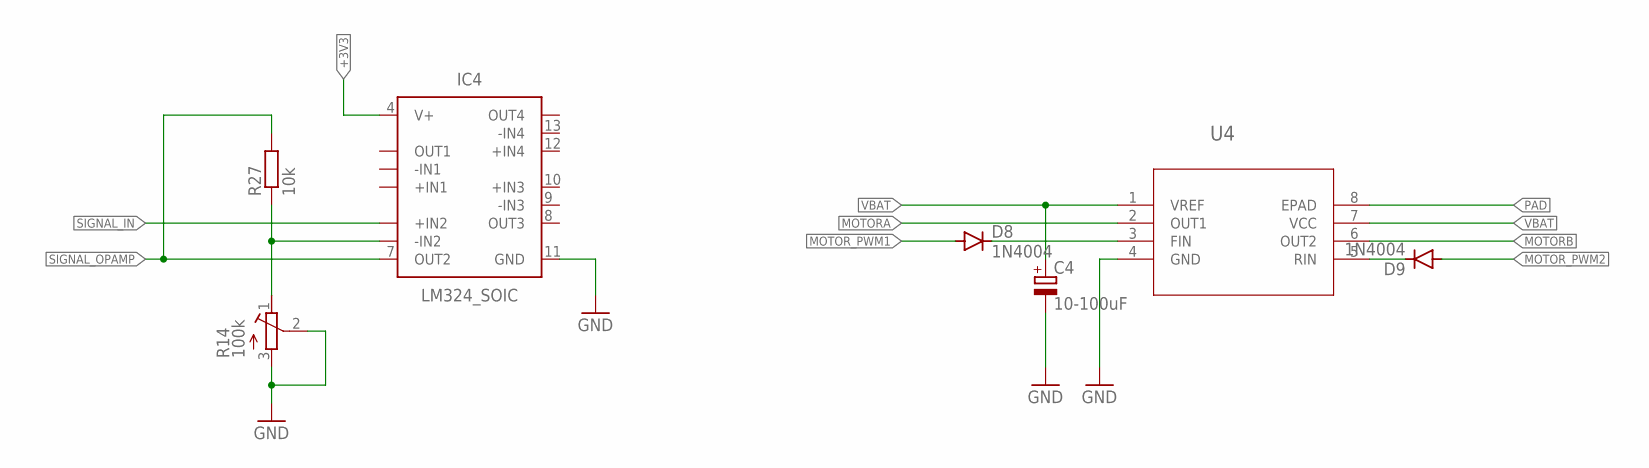
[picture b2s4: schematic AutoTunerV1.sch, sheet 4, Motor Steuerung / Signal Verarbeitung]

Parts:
C4: 10-100uF; B45181A
D8, D9: 1N4004; DO41-10
IC4: LM324_SOIC; SOIC127P600X175-14N; LCSC_PART C71035
R14: 100k; RTRIM43P
R27: 10k; R0805
U4: BD6222HFP-TRHRP7_ROM-M; HRP7_ROM-M

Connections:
+3V3: IC4.4 (V+); also elsewhere on the board
GND: C4.-, IC4.11 (GND), R14.2 (S), R14.3 (A), U4.4 (GND); also elsewhere on the board
MOTORA: U4.2 (OUT1); also elsewhere on the board
MOTORB: U4.6 (OUT2); also elsewhere on the board
MOTOR_PWM1: D8.A; also elsewhere on the board
MOTOR_PWM2: D9.A; also elsewhere on the board
unnamed: D8.C, U4.3 (FIN)
unnamed: D9.C, U4.5 (RIN)
unnamed: IC4.6 (-IN2), R14.1 (E), R27.1
PAD: U4.8 (EPAD)
SIGNAL_IN: IC4.5 (+IN2); also elsewhere on the board
SIGNAL_OPAMP: IC4.7 (OUT2), R27.2; also elsewhere on the board
VBAT: C4.+, U4.1 (VREF); also elsewhere on the board

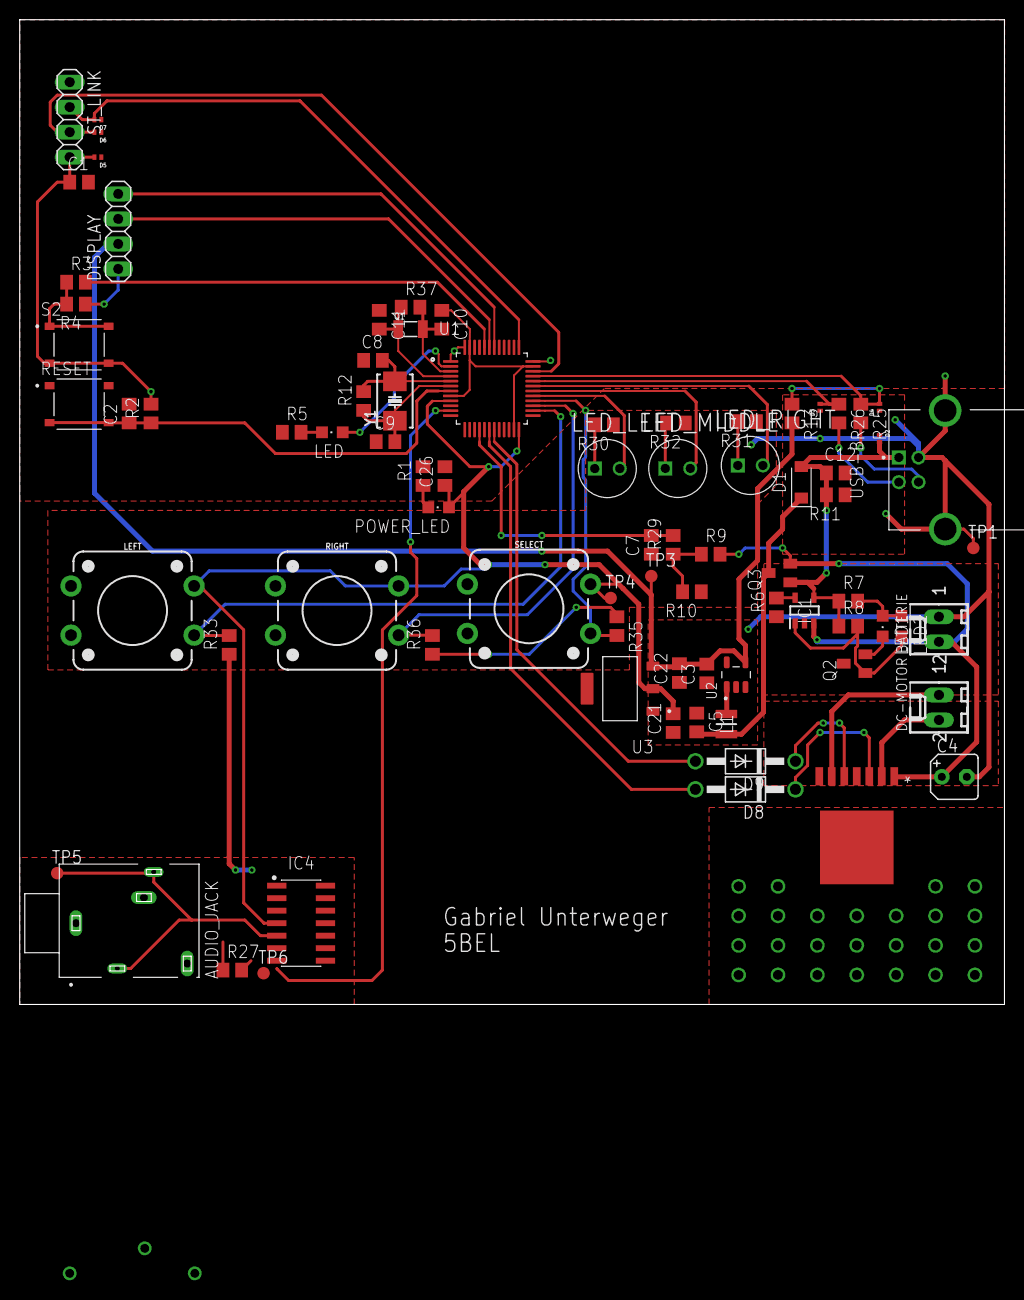
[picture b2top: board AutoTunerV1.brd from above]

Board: 2 copper layers, 100.0 x 100.0 mm, 82 parts (1 on the bottom side), 49 nets.

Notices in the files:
parts and their libraries:
crystal-geyer_V1_0: Copyright: Geyer-Electronic
SparkFun-Switches: Licensing: Creative Commons ShareAlike 4.0 International - https://creativecommons.org/licenses/by-sa/4.0
COPYRIGHT: Copyright (C) 2022 Ultra Librarian. All rights reserved.
